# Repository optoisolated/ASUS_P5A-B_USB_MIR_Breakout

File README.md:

# ASUS P5A-B USB/MIR Breakout Board
Asus P5A-B USB/MIR Breakout Board Replacement

Based on the original Asus Breakout board, which are no longer available, this PCB is a near identical replica of the original board. It is designed to break out the PS/2 Mouse, Infrared and Dual USB Connectors on the Motherboard, to the back of the computer case.

Forum: https://www.vogons.org/viewtopic.php?f=46&t=78592&start=20

## Included:
* Kicad PCB Files
* Kicad Schematic
* GERBER Files

## Exerpt from the ASUS P5A-B manual referring to the USB/MIR Breakout

## Render of the new replacement board

## TODO: 
* Build and Test
* Validate Capacitor values (default values should be okay, but they are untested)

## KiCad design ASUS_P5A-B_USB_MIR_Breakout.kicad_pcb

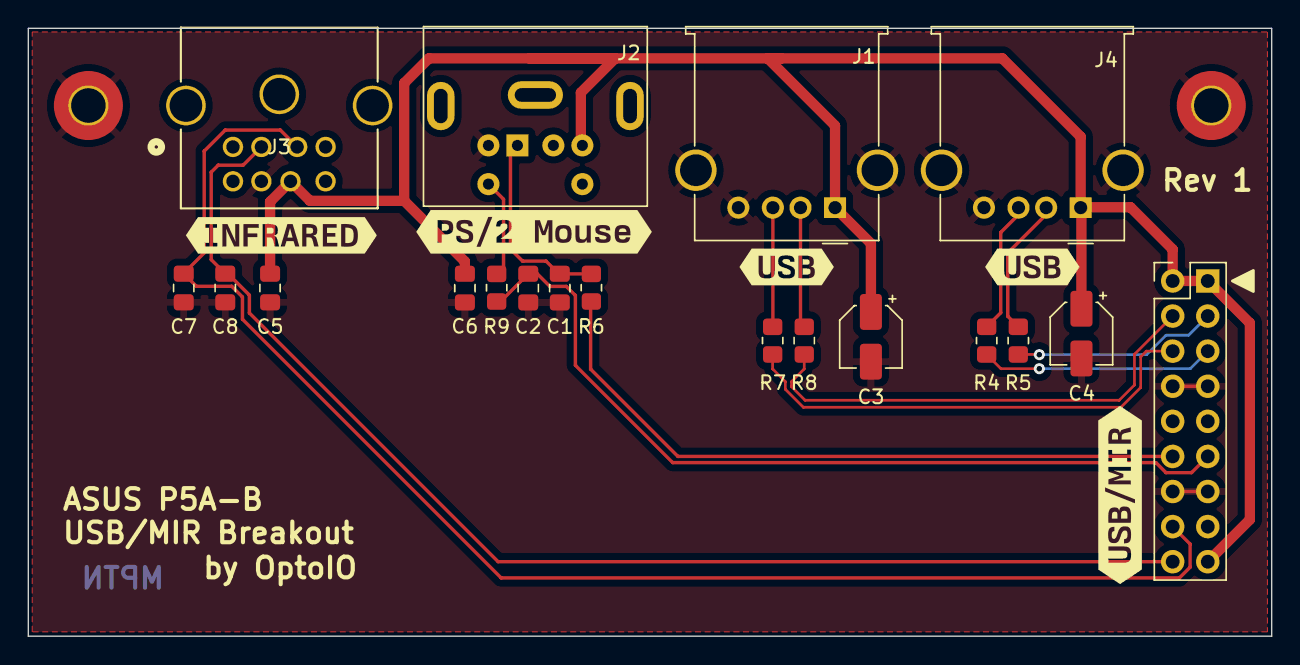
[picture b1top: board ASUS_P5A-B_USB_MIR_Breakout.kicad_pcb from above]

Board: 2 copper layers, 90.0 x 44.0 mm, 26 parts (0 on the bottom side), 16 nets.

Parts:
C1, C2, C5, C6, C7, C8: C; C_0805_2012Metric_Pad1.18x1.45mm_HandSolder
C3, C4: 0.1u; CP_Elec_4x5.3
H1, H2: GND; MountingHole_2.5mm_Pad_TopBottom
J1, J4: USB_A; USB_A_Molex_67643_Horizontal
J2: MOUSE PS/2; Connector_Mini-DIN_Female_6Pin_2rows
J3: INFRA RED; CONN8_1658998-1_TEC
J6: USB/MIR; PinHeader_2x09_P2.54mm_Vertical
R4, R5, R6, R7, R8, R9: 0.1; R_0805_2012Metric_Pad1.20x1.40mm_HandSolder
kibuzzard-660BC1F4: G***; kibuzzard-660BC1F4
kibuzzard-660BC208: G***; kibuzzard-660BC208
kibuzzard-660BC226, kibuzzard-660BC226#2: G***; kibuzzard-660BC226
kibuzzard-660BC248: G***; kibuzzard-660BC248

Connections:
+5V: C3.1, C4.1, C5.1, C6.1, J1.1 (VBUS), J2.4, J3.7, J4.1 (VBUS), J6.1, J6.9, J6.10
/IR_RX: C7.1, J3.2, J6.17
/IR_TX: C8.1, J3.1, J6.18
/MOUSE_CLK: C2.1, J6.6, R9.2
/MOUSE_DATA: J6.15, R6.2
/USB1_D+: J6.3, R4.2
/USB1_D-: J6.2, R5.2
/USB2_D+: J6.12, R7.2
/USB2_D-: J6.11, R8.2
GND: C1.2, C2.2, C3.2, C4.2, C5.2, C6.2, C7.2, C8.2, H1.1, H2.1, J1.4 (GND), J1.5 (Shield), J2.3, J3.4, J4.4 (GND), J4.5 (Shield), J6.4, J6.7, J6.13, J6.16
unnamed: C1.1, J2.1, R6.1
unnamed: J1.3 (D+), R7.1
unnamed: J1.2 (D-), R8.1
unnamed: J2.5, R9.1
unnamed: J4.3 (D+), R4.1
unnamed: J4.2 (D-), R5.1

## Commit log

2024-04-02 Initial Commit
    Complete Initial Commit
